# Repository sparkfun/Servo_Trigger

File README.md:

SparkFun Servo Trigger
========================================

[*SparkFun Servo Trigger (WIG-13118)*](https://www.sparkfun.com/products/13118)

The SparkFun Servo Trigger is a small robotics board that simplifies the control of hobby RC servo motors. 
When an external switch or logic signal changes state, the Servo Trigger is able to tell an attached servo motor to move from position A to position B. 
To use the Servo Trigger, you simply connect a hobby servo and a switch, then use the on-board potentiometers to adjust the start/stop positions and the transition time. 

Repository Contents
-------------------
* **/Docs** -  Programming notes
* **/Firmware** - Example firmware for running the Servo Trigger
* **/Hardware** - All Eagle design files (.brd, .sch)
* **/Production** - Test bed files and production panel files

License Information
-------------------
The hardware is released under [Creative Commons ShareAlike 4.0 International](https://creativecommons.org/licenses/by-sa/4.0/).
The code is beerware; if you see me (or any other SparkFun employee) at the local, and you've found our code helpful, please buy us a round!

Distributed as-is; no warranty is given.

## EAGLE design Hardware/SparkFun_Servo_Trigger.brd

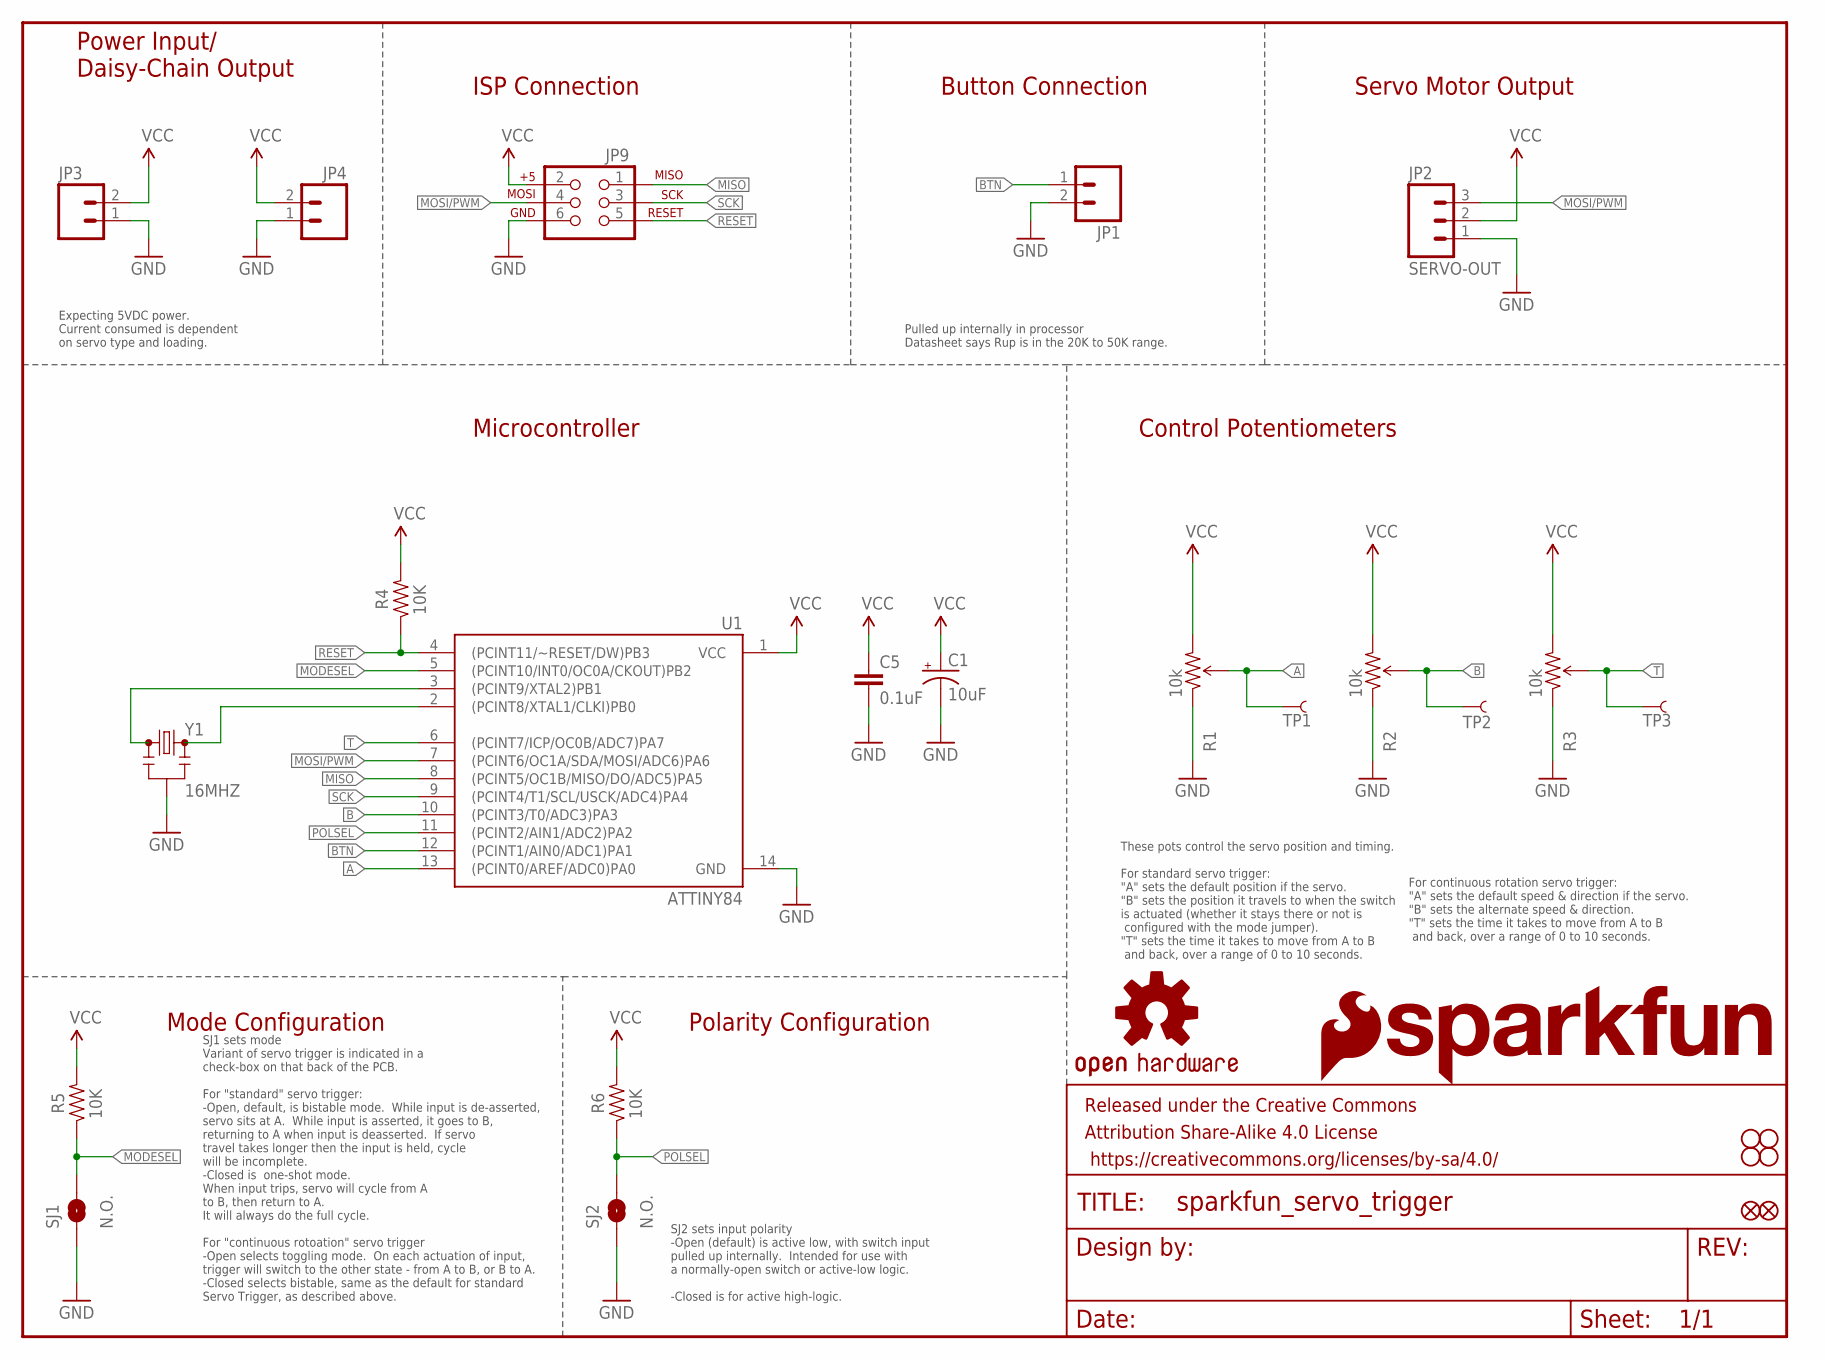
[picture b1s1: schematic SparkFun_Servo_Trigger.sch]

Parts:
C1: 10uF; EIA3216
C5: 0.1uF; 0603-CAP
FID1, FID2: FIDUCIAL1X2; FIDUCIAL-1X2
FRAME1: frame; CREATIVE_COMMONS
JP1, JP3, JP4: M021X02_NO_SILK; 1X02_NO_SILK
JP2: SERVO-OUT; 1X03_NO_SILK
JP9: AVR_SPI_PRG_6PTH; 2X3
LOGO1: OSHW-LOGOM; OSHW-LOGO-M
LOGO2: SFE_LOGO_NAME.2_INCH; SFE_LOGO_NAME_.2
LOGO3: SFE_LOGO_FLAME.2_INCH; SFE_LOGO_FLAME_.2
R1, R2, R3: 10k; TRIMPOT_5MM
R4, R5, R6: 10K; 0603-RES
SJ1, SJ2: N.O.; PAD-JUMPER-2-NO_YES_SILK
STANDOFF1, STANDOFF2, STANDOFF3, STANDOFF4: STAND-OFF
TP1, TP2, TP3: TEST-POINT3X4; PAD.03X.04
U1: ATTINY84; SO14
Y1: 16MHZ; RESONATOR-SMD

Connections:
A: R1.B (WIPER), TP1.P$1, U1.13 ((PCINT0/AREF/ADC0)PA0)
B: R2.B (WIPER), TP2.P$1, U1.10 ((PCINT3/T0/ADC3)PA3)
BTN: JP1.1, U1.12 ((PCINT1/AIN0/ADC1)PA1)
GND: C1.C (-), C5.2, JP1.2, JP2.1, JP3.1, JP4.1, JP9.6, R1.A (CCW), R2.A (CCW), R3.A (CCW), SJ1.1, SJ2.1, U1.14 (GND), Y1.2
MISO: JP9.1, U1.8 ((PCINT5/OC1B/MISO/DO/ADC5)PA5)
MODESEL: R5.1, SJ1.2, U1.5 ((PCINT10/INT0/OC0A/CKOUT)PB2)
MOSI/PWM: JP2.3, JP9.4, U1.7 ((PCINT6/OC1A/SDA/MOSI/ADC6)PA6)
unnamed: U1.3 ((PCINT9/XTAL2)PB1), Y1.1
unnamed: U1.2 ((PCINT8/XTAL1/CLKI)PB0), Y1.3
POLSEL: R6.1, SJ2.2, U1.11 ((PCINT2/AIN1/ADC2)PA2)
RESET: JP9.5, R4.1, U1.4 ((PCINT11/~RESET/DW)PB3)
SCK: JP9.3, U1.9 ((PCINT4/T1/SCL/USCK/ADC4)PA4)
T: R3.B (WIPER), TP3.P$1, U1.6 ((PCINT7/ICP/OC0B/ADC7)PA7)
VCC: C1.A (+), C5.1, JP2.2, JP3.2, JP4.2, JP9.2, R1.C (CW), R2.C (CW), R3.C (CW), R4.2, R5.2, R6.2, U1.1 (VCC)

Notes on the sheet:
Power Input/ Daisy-Chain Output
ISP Connection
Control Potentiometers
Microcontroller
Button Connection
Servo Motor Output
Mode Configuration
Polarity Configuration
SJ1 sets mode Variant of servo trigger is indicated in a check-box on that back of the PCB. For "standard" servo trigger: -Open, default, is bistable mode. While input is de-asserted, servo sits at A. While input is asserted, it goes to B, returning to A when input is deasserted. If servo travel ta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
SJ2 sets input polarity -Open (default) is active low, with switch input pulled up internally. Intended for use with a normally-open switch or active-low logic. -Closed is for active high-logic.
Pulled up internally in processor Datasheet says Rup is in the 20K to 50K range.
Expecting 5VDC power. Current consumed is dependent on servo type and loading.
These pots control the servo position and timing. For standard servo trigger: "A" sets the default position if the servo. "B" sets the position it travels to when the switch is actuated (whether it stays there or not is configured with the mode jumper). "T" sets the time it takes to move from A to 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
For continuous rotation servo trigger: "A" sets the default speed & direction if the servo. "B" sets the alternate speed & direction. "T" sets the time it takes to move from A to B and back, over a range of 0 to 10 seconds.

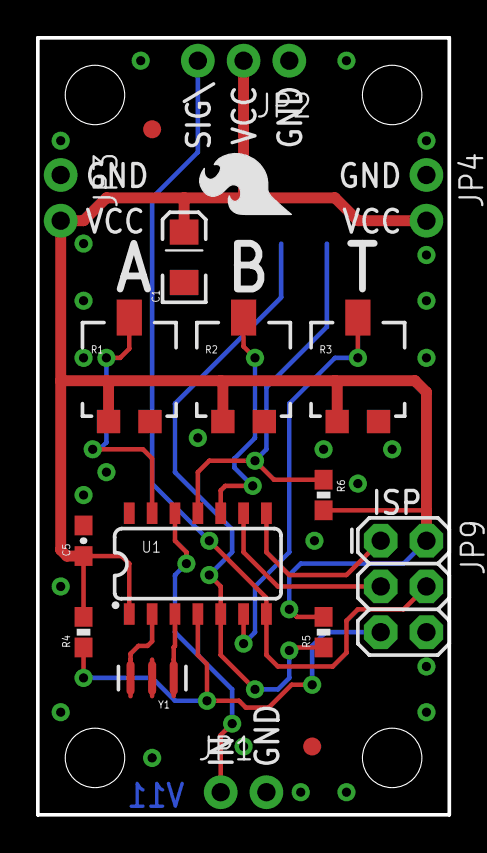
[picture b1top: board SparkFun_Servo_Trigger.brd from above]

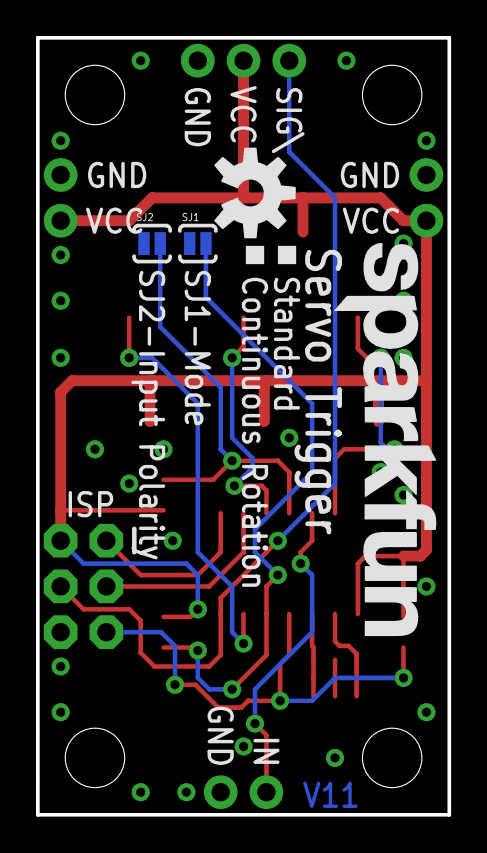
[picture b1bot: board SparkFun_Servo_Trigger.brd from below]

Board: 2 copper layers, 22.9 x 43.2 mm, 30 parts (7 on the bottom side), 14 nets.

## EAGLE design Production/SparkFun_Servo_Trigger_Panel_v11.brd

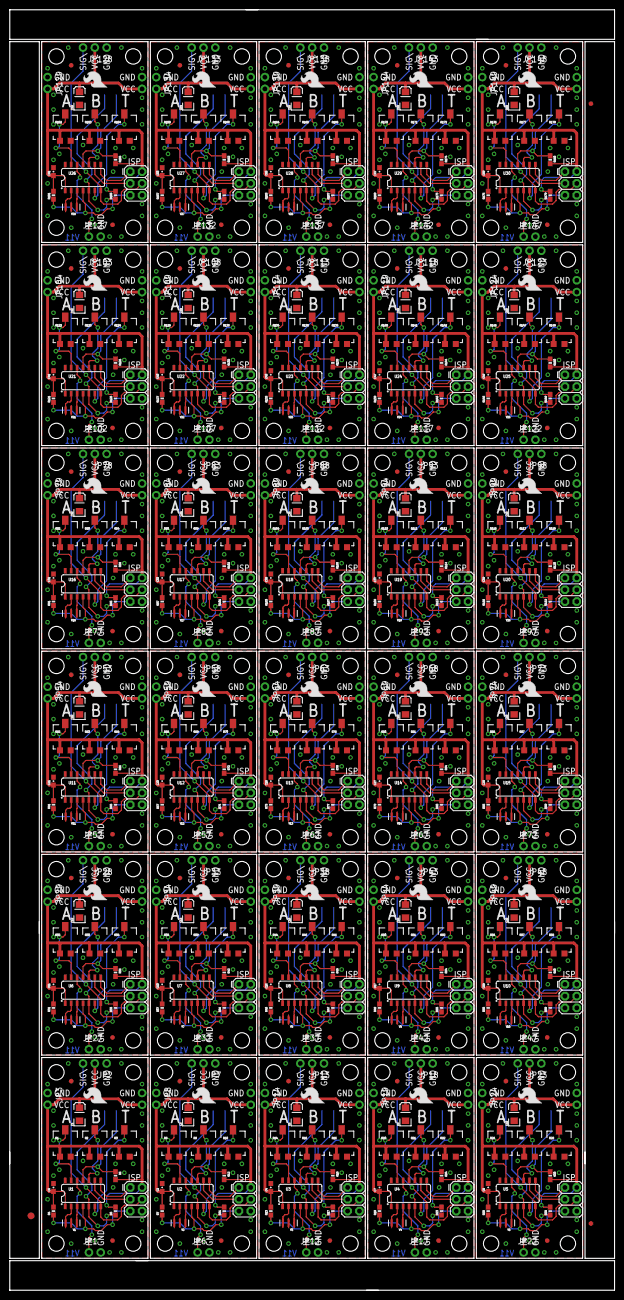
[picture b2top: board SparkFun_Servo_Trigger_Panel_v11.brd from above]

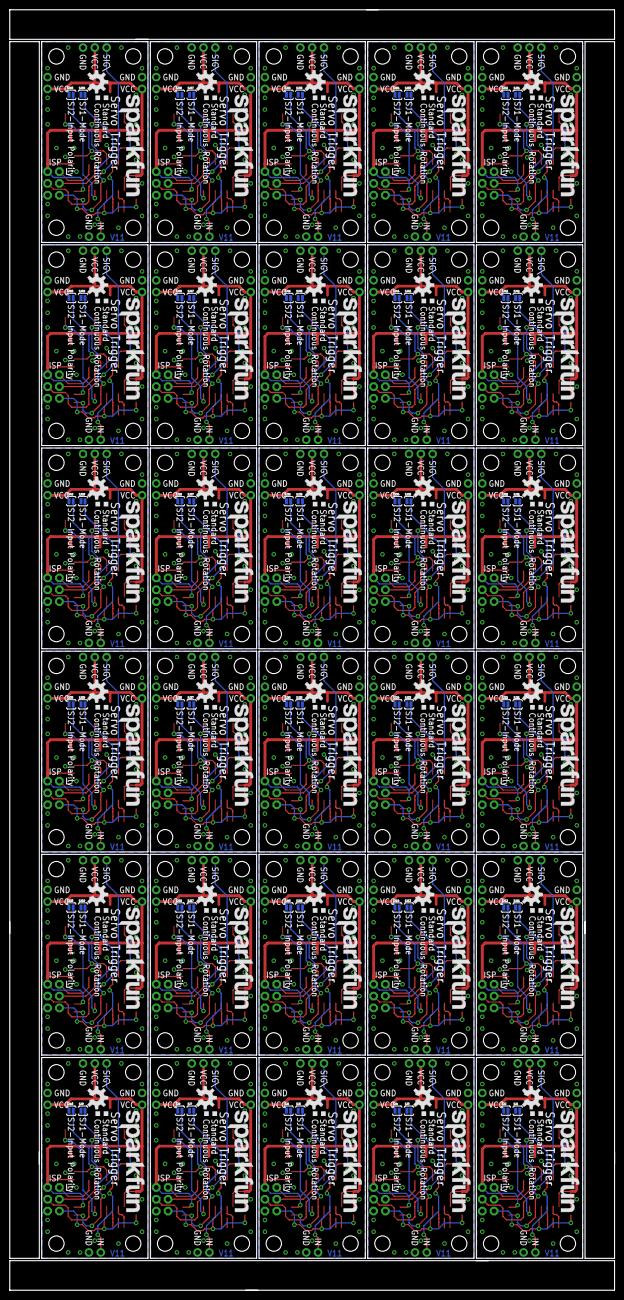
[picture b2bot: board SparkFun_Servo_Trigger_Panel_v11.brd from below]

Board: 2 copper layers, 130.0 x 275.3 mm, 873 parts (210 on the bottom side), 420 nets.

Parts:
C1, C3, C6, C8, C10, C12, C14, C16, C18, C20, C22, C24, C26, C28, C30, C32, C34, C36, C38, C40, C42, C44, C46, C48, C50, C52, C54, C56, C58, C60: 10uF; EIA3216
C2, C4, C5, C7, C9, C11, C13, C15, C17, C19, C21, C23, C25, C27, C29, C31, C33, C35, C37, C39, C41, C43, C45, C47, C49, C51, C53, C55, C57, C59: 0.1uF; 0603-CAP
E$1: FIDUCIAL-1.5X3
E$7, E$8: FIDUCIAL-1X2
FID1, FID2, FID3, FID4, FID5, FID6, FID7, FID8, FID9, FID10, FID11, FID12, FID13, FID14, FID15, FID16, FID17, FID18, FID19, FID20, FID21, FID22, FID23, FID24, FID25, FID26, FID27, FID28, FID29, FID30, FID31, FID32, FID33, FID34, FID35, FID36, FID37, FID38, FID39, FID40, FID41, FID42, FID43, FID44, FID45, FID46, FID47, FID48, FID49, FID50, FID51, FID52, FID53, FID54, FID55, FID56, FID57, FID58, FID59, FID60: FIDUCIAL1X2; FIDUCIAL-1X2
JP1, JP3, JP4, JP6, JP8, JP10, JP12, JP14, JP15, JP17, JP19, JP20, JP22, JP24, JP25, JP27, JP29, JP30, JP32, JP34, JP35, JP37, JP39, JP40, JP42, JP44, JP45, JP47, JP49, JP50, JP52, JP54, JP55, JP57, JP59, JP60, JP62, JP64, JP65, JP67, JP69, JP70, JP72, JP74, JP75, JP77, JP79, JP80, JP82, JP84, JP85, JP87, JP89, JP90, JP92, JP94, JP95, JP97, JP99, JP100, JP102, JP104, JP105, JP107, JP109, JP110, JP112, JP114, JP115, JP117, JP119, JP120, JP122, JP124, JP125, JP127, JP129, JP130, JP132, JP134, JP135, JP137, JP139, JP140, JP142, JP144, JP145, JP147, JP149, JP150: M021X02_NO_SILK; 1X02_NO_SILK
JP2, JP7, JP13, JP18, JP23, JP28, JP33, JP38, JP43, JP48, JP53, JP58, JP63, JP68, JP73, JP78, JP83, JP88, JP93, JP98, JP103, JP108, JP113, JP118, JP123, JP128, JP133, JP138, JP143, JP148: SERVO-OUT; 1X03_NO_SILK
JP5, JP9, JP11, JP16, JP21, JP26, JP31, JP36, JP41, JP46, JP51, JP56, JP61, JP66, JP71, JP76, JP81, JP86, JP91, JP96, JP101, JP106, JP111, JP116, JP121, JP126, JP131, JP136, JP141, JP146: 2X3
LOGO1, LOGO4, LOGO7, LOGO10, LOGO13, LOGO16, LOGO19, LOGO22, LOGO25, LOGO28, LOGO31, LOGO34, LOGO37, LOGO40, LOGO43, LOGO46, LOGO49, LOGO52, LOGO55, LOGO58, LOGO61, LOGO64, LOGO67, LOGO70, LOGO73, LOGO76, LOGO79, LOGO82, LOGO85, LOGO88: OSHW-LOGOM; OSHW-LOGO-M
LOGO2, LOGO5, LOGO8, LOGO11, LOGO14, LOGO17, LOGO20, LOGO23, LOGO26, LOGO29, LOGO32, LOGO35, LOGO38, LOGO41, LOGO44, LOGO47, LOGO50, LOGO53, LOGO56, LOGO59, LOGO62, LOGO65, LOGO68, LOGO71, LOGO74, LOGO77, LOGO80, LOGO83, LOGO86, LOGO89: SFE_LOGO_NAME.2_INCH; SFE_LOGO_NAME_.2
LOGO3, LOGO6, LOGO9, LOGO12, LOGO15, LOGO18, LOGO21, LOGO24, LOGO27, LOGO30, LOGO33, LOGO36, LOGO39, LOGO42, LOGO45, LOGO48, LOGO51, LOGO54, LOGO57, LOGO60, LOGO63, LOGO66, LOGO69, LOGO72, LOGO75, LOGO78, LOGO81, LOGO84, LOGO87, LOGO90: SFE_LOGO_FLAME.2_INCH; SFE_LOGO_FLAME_.2
R1, R2, R3, R8, R9, R10, R14, R15, R16, R20, R21, R22, R26, R27, R28, R32, R33, R34, R38, R39, R40, R44, R45, R46, R50, R51, R52, R56, R57, R58, R62, R63, R64, R68, R69, R70, R74, R75, R76, R80, R81, R82, R86, R87, R88, R92, R93, R94, R98, R99, R100, R104, R105, R106, R110, R111, R112, R116, R117, R118, R122, R123, R124, R128, R129, R130, R134, R135, R136, R140, R141, R142, R146, R147, R148, R152, R153, R154, R158, R159, R160, R164, R165, R166, R170, R171, R172, R176, R177, R178: 10k; TRIMPOT_5MM
R4, R5, R6, R7, R11, R12, R13, R17, R18, R19, R23, R24, R25, R29, R30, R31, R35, R36, R37, R41, R42, R43, R47, R48, R49, R53, R54, R55, R59, R60, R61, R65, R66, R67, R71, R72, R73, R77, R78, R79, R83, R84, R85, R89, R90, R91, R95, R96, R97, R101, R102, R103, R107, R108, R109, R113, R114, R115, R119, R120, R121, R125, R126, R127, R131, R132, R133, R137, R138, R139, R143, R144, R145, R149, R150, R151, R155, R156, R157, R161, R162, R163, R167, R168, R169, R173, R174, R175, R179, R180: 10K; 0603-RES
SJ1, SJ2, SJ3, SJ4, SJ5, SJ6, SJ7, SJ8, SJ9, SJ10, SJ11, SJ12, SJ13, SJ14, SJ15, SJ16, SJ17, SJ18, SJ19, SJ20, SJ21, SJ22, SJ23, SJ24, SJ25, SJ26, SJ27, SJ28, SJ29, SJ30, SJ31, SJ32, SJ33, SJ34, SJ35, SJ36, SJ37, SJ38, SJ39, SJ40, SJ41, SJ42, SJ43, SJ44, SJ45, SJ46, SJ47, SJ48, SJ49, SJ50, SJ51, SJ52, SJ53, SJ54, SJ55, SJ56, SJ57, SJ58, SJ59, SJ60: N.O.; PAD-JUMPER-2-NO_YES_SILK
STANDOFF1, STANDOFF2, STANDOFF3, STANDOFF4, STANDOFF5, STANDOFF6, STANDOFF7, STANDOFF8, STANDOFF9, STANDOFF10, STANDOFF11, STANDOFF12, STANDOFF13, STANDOFF14, STANDOFF15, STANDOFF16, STANDOFF17, STANDOFF18, STANDOFF19, STANDOFF20, STANDOFF21, STANDOFF22, STANDOFF23, STANDOFF24, STANDOFF25, STANDOFF26, STANDOFF27, STANDOFF28, STANDOFF29, STANDOFF30, STANDOFF31, STANDOFF32, STANDOFF33, STANDOFF34, STANDOFF35, STANDOFF36, STANDOFF37, STANDOFF38, STANDOFF39, STANDOFF40, STANDOFF41, STANDOFF42, STANDOFF43, STANDOFF44, STANDOFF45, STANDOFF46, STANDOFF47, STANDOFF48, STANDOFF49, STANDOFF50, STANDOFF51, STANDOFF52, STANDOFF53, STANDOFF54, STANDOFF55, STANDOFF56, STANDOFF57, STANDOFF58, STANDOFF59, STANDOFF60, STANDOFF61, STANDOFF62, STANDOFF63, STANDOFF64, STANDOFF65, STANDOFF66, STANDOFF67, STANDOFF68, STANDOFF69, STANDOFF70, STANDOFF71, STANDOFF72, STANDOFF73, STANDOFF74, STANDOFF75, STANDOFF76, STANDOFF77, STANDOFF78, STANDOFF79, STANDOFF80, STANDOFF81, STANDOFF82, STANDOFF83, STANDOFF84, STANDOFF85, STANDOFF86, STANDOFF87, STANDOFF88, STANDOFF89, STANDOFF90, STANDOFF91, STANDOFF92, STANDOFF93, STANDOFF94, STANDOFF95, STANDOFF96, STANDOFF97, STANDOFF98, STANDOFF99, STANDOFF100, STANDOFF101, STANDOFF102, STANDOFF103, STANDOFF104, STANDOFF105, STANDOFF106, STANDOFF107, STANDOFF108, STANDOFF109, STANDOFF110, STANDOFF111, STANDOFF112, STANDOFF113, STANDOFF114, STANDOFF115, STANDOFF116, STANDOFF117, STANDOFF118, STANDOFF119, STANDOFF120: STAND-OFF
TP1, TP2, TP3, TP4, TP5, TP6, TP7, TP8, TP9, TP10, TP11, TP12, TP13, TP14, TP15, TP16, TP17, TP18, TP19, TP20, TP21, TP22, TP23, TP24, TP25, TP26, TP27, TP28, TP29, TP30, TP31, TP32, TP33, TP34, TP35, TP36, TP37, TP38, TP39, TP40, TP41, TP42, TP43, TP44, TP45, TP46, TP47, TP48, TP49, TP50, TP51, TP52, TP53, TP54, TP55, TP56, TP57, TP58, TP59, TP60, TP61, TP62, TP63, TP64, TP65, TP66, TP67, TP68, TP69, TP70, TP71, TP72, TP73, TP74, TP75, TP76, TP77, TP78, TP79, TP80, TP81, TP82, TP83, TP84, TP85, TP86, TP87, TP88, TP89, TP90: TEST-POINT3X4; PAD.03X.04
U1, U2, U3, U4, U5, U6, U7, U8, U9, U10, U11, U12, U13, U14, U15, U16, U17, U18, U19, U20, U21, U22, U23, U24, U25, U26, U27, U28, U29, U30: ATTINY84; SO14
Y1, Y2, Y3, Y4, Y5, Y6, Y7, Y8, Y9, Y10, Y11, Y12, Y13, Y14, Y15, Y16, Y17, Y18, Y19, Y20, Y21, Y22, Y23, Y24, Y25, Y26, Y27, Y28, Y29, Y30: 16MHZ; RESONATOR-SMD

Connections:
A: R1.B, TP1.P$1, U1.13
A1: R8.B, TP4.P$1, U2.13
A2: R14.B, TP7.P$1, U3.13
A3: R20.B, TP10.P$1, U4.13
A4: R26.B, TP13.P$1, U5.13
A5: R32.B, TP16.P$1, U6.13
A6: R38.B, TP19.P$1, U7.13
A7: R44.B, TP22.P$1, U8.13
A8: R50.B, TP25.P$1, U9.13
A9: R56.B, TP28.P$1, U10.13
A10: R62.B, TP31.P$1, U11.13
A11: R68.B, TP34.P$1, U12.13
A12: R74.B, TP37.P$1, U13.13
A13: R80.B, TP40.P$1, U14.13
A14: R86.B, TP43.P$1, U15.13
A15: R92.B, TP46.P$1, U16.13
A16: R98.B, TP49.P$1, U17.13
A17: R104.B, TP52.P$1, U18.13
A18: R110.B, TP55.P$1, U19.13
A19: R116.B, TP58.P$1, U20.13
A20: R122.B, TP61.P$1, U21.13
A21: R128.B, TP64.P$1, U22.13
A22: R134.B, TP67.P$1, U23.13
A23: R140.B, TP70.P$1, U24.13
A24: R146.B, TP73.P$1, U25.13
A25: R152.B, TP76.P$1, U26.13
A26: R158.B, TP79.P$1, U27.13
A27: R164.B, TP82.P$1, U28.13
A28: R170.B, TP85.P$1, U29.13
A29: R176.B, TP88.P$1, U30.13
B: R2.B, TP2.P$1, U1.10
B1: R9.B, TP5.P$1, U2.10
B2: R15.B, TP8.P$1, U3.10
B3: R21.B, TP11.P$1, U4.10
B4: R27.B, TP14.P$1, U5.10
B5: R33.B, TP17.P$1, U6.10
B6: R39.B, TP20.P$1, U7.10
B7: R45.B, TP23.P$1, U8.10
B8: R51.B, TP26.P$1, U9.10
B9: R57.B, TP29.P$1, U10.10
B10: R63.B, TP32.P$1, U11.10
B11: R69.B, TP35.P$1, U12.10
B12: R75.B, TP38.P$1, U13.10
B13: R81.B, TP41.P$1, U14.10
B14: R87.B, TP44.P$1, U15.10
B15: R93.B, TP47.P$1, U16.10
B16: R99.B, TP50.P$1, U17.10
B17: R105.B, TP53.P$1, U18.10
B18: R111.B, TP56.P$1, U19.10
B19: R117.B, TP59.P$1, U20.10
B20: R123.B, TP62.P$1, U21.10
B21: R129.B, TP65.P$1, U22.10
B22: R135.B, TP68.P$1, U23.10
B23: R141.B, TP71.P$1, U24.10
B24: R147.B, TP74.P$1, U25.10
B25: R153.B, TP77.P$1, U26.10
B26: R159.B, TP80.P$1, U27.10
B27: R165.B, TP83.P$1, U28.10
B28: R171.B, TP86.P$1, U29.10
B29: R177.B, TP89.P$1, U30.10
BTN: JP1.1, U1.12
BTN1: JP6.1, U2.12
BTN2: JP12.1, U3.12
BTN3: JP17.1, U4.12
BTN4: JP22.1, U5.12
BTN5: JP27.1, U6.12
BTN6: JP32.1, U7.12
BTN7: JP37.1, U8.12
BTN8: JP42.1, U9.12
BTN9: JP47.1, U10.12
BTN10: JP52.1, U11.12
BTN11: JP57.1, U12.12
BTN12: JP62.1, U13.12
BTN13: JP67.1, U14.12
BTN14: JP72.1, U15.12
BTN15: JP77.1, U16.12
BTN16: JP82.1, U17.12
BTN17: JP87.1, U18.12
BTN18: JP92.1, U19.12
BTN19: JP97.1, U20.12
BTN20: JP102.1, U21.12
BTN21: JP107.1, U22.12
BTN22: JP112.1, U23.12
BTN23: JP117.1, U24.12
BTN24: JP122.1, U25.12
BTN25: JP127.1, U26.12
BTN26: JP132.1, U27.12
BTN27: JP137.1, U28.12
BTN28: JP142.1, U29.12
BTN29: JP147.1, U30.12
GND: C1.C, C5.2, JP1.2, JP2.1, JP3.1, JP4.1, JP9.6, R1.A, R2.A, R3.A, SJ1.1, SJ2.1, U1.14, Y1.2
GND1: C2.2, C3.C, JP5.6, JP6.2, JP7.1, JP8.1, JP10.1, R8.A, R9.A, R10.A, SJ3.1, SJ4.1, U2.14, Y2.2
GND2: C4.2, C6.C, JP11.6, JP12.2, JP13.1, JP14.1, JP15.1, R14.A, R15.A, R16.A, SJ5.1, SJ6.1, U3.14, Y3.2
GND3: C7.2, C8.C, JP16.6, JP17.2, JP18.1, JP19.1, JP20.1, R20.A, R21.A, R22.A, SJ7.1, SJ8.1, U4.14, Y4.2
GND4: C9.2, C10.C, JP21.6, JP22.2, JP23.1, JP24.1, JP25.1, R26.A, R27.A, R28.A, SJ9.1, SJ10.1, U5.14, Y5.2
GND5: C11.2, C12.C, JP26.6, JP27.2, JP28.1, JP29.1, JP30.1, R32.A, R33.A, R34.A, SJ11.1, SJ12.1, U6.14, Y6.2
GND6: C13.2, C14.C, JP31.6, JP32.2, JP33.1, JP34.1, JP35.1, R38.A, R39.A, R40.A, SJ13.1, SJ14.1, U7.14, Y7.2
GND7: C15.2, C16.C, JP36.6, JP37.2, JP38.1, JP39.1, JP40.1, R44.A, R45.A, R46.A, SJ15.1, SJ16.1, U8.14, Y8.2
GND8: C17.2, C18.C, JP41.6, JP42.2, JP43.1, JP44.1, JP45.1, R50.A, R51.A, R52.A, SJ17.1, SJ18.1, U9.14, Y9.2
GND9: C19.2, C20.C, JP46.6, JP47.2, JP48.1, JP49.1, JP50.1, R56.A, R57.A, R58.A, SJ19.1, SJ20.1, U10.14, Y10.2
GND10: C21.2, C22.C, JP51.6, JP52.2, JP53.1, JP54.1, JP55.1, R62.A, R63.A, R64.A, SJ21.1, SJ22.1, U11.14, Y11.2
GND11: C23.2, C24.C, JP56.6, JP57.2, JP58.1, JP59.1, JP60.1, R68.A, R69.A, R70.A, SJ23.1, SJ24.1, U12.14, Y12.2
GND12: C25.2, C26.C, JP61.6, JP62.2, JP63.1, JP64.1, JP65.1, R74.A, R75.A, R76.A, SJ25.1, SJ26.1, U13.14, Y13.2
GND13: C27.2, C28.C, JP66.6, JP67.2, JP68.1, JP69.1, JP70.1, R80.A, R81.A, R82.A, SJ27.1, SJ28.1, U14.14, Y14.2
GND14: C29.2, C30.C, JP71.6, JP72.2, JP73.1, JP74.1, JP75.1, R86.A, R87.A, R88.A, SJ29.1, SJ30.1, U15.14, Y15.2
GND15: C31.2, C32.C, JP76.6, JP77.2, JP78.1, JP79.1, JP80.1, R92.A, R93.A, R94.A, SJ31.1, SJ32.1, U16.14, Y16.2
GND16: C33.2, C34.C, JP81.6, JP82.2, JP83.1, JP84.1, JP85.1, R98.A, R99.A, R100.A, SJ33.1, SJ34.1, U17.14, Y17.2
GND17: C35.2, C36.C, JP86.6, JP87.2, JP88.1, JP89.1, JP90.1, R104.A, R105.A, R106.A, SJ35.1, SJ36.1, U18.14, Y18.2
GND18: C37.2, C38.C, JP91.6, JP92.2, JP93.1, JP94.1, JP95.1, R110.A, R111.A, R112.A, SJ37.1, SJ38.1, U19.14, Y19.2
GND19: C39.2, C40.C, JP96.6, JP97.2, JP98.1, JP99.1, JP100.1, R116.A, R117.A, R118.A, SJ39.1, SJ40.1, U20.14, Y20.2
GND20: C41.2, C42.C, JP101.6, JP102.2, JP103.1, JP104.1, JP105.1, R122.A, R123.A, R124.A, SJ41.1, SJ42.1, U21.14, Y21.2
GND21: C43.2, C44.C, JP106.6, JP107.2, JP108.1, JP109.1, JP110.1, R128.A, R129.A, R130.A, SJ43.1, SJ44.1, U22.14, Y22.2
GND22: C45.2, C46.C, JP111.6, JP112.2, JP113.1, JP114.1, JP115.1, R134.A, R135.A, R136.A, SJ45.1, SJ46.1, U23.14, Y23.2
GND23: C47.2, C48.C, JP116.6, JP117.2, JP118.1, JP119.1, JP120.1, R140.A, R141.A, R142.A, SJ47.1, SJ48.1, U24.14, Y24.2
GND24: C49.2, C50.C, JP121.6, JP122.2, JP123.1, JP124.1, JP125.1, R146.A, R147.A, R148.A, SJ49.1, SJ50.1, U25.14, Y25.2
GND25: C51.2, C52.C, JP126.6, JP127.2, JP128.1, JP129.1, JP130.1, R152.A, R153.A, R154.A, SJ51.1, SJ52.1, U26.14, Y26.2
GND26: C53.2, C54.C, JP131.6, JP132.2, JP133.1, JP134.1, JP135.1, R158.A, R159.A, R160.A, SJ53.1, SJ54.1, U27.14, Y27.2
GND27: C55.2, C56.C, JP136.6, JP137.2, JP138.1, JP139.1, JP140.1, R164.A, R165.A, R166.A, SJ55.1, SJ56.1, U28.14, Y28.2
GND28: C57.2, C58.C, JP141.6, JP142.2, JP143.1, JP144.1, JP145.1, R170.A, R171.A, R172.A, SJ57.1, SJ58.1, U29.14, Y29.2
GND29: C59.2, C60.C, JP146.6, JP147.2, JP148.1, JP149.1, JP150.1, R176.A, R177.A, R178.A, SJ59.1, SJ60.1, U30.14, Y30.2
MISO: JP9.1, U1.8
MISO1: JP5.1, U2.8
MISO2: JP11.1, U3.8
MISO3: JP16.1, U4.8
MISO4: JP21.1, U5.8
MISO5: JP26.1, U6.8
MISO6: JP31.1, U7.8
MISO7: JP36.1, U8.8
MISO8: JP41.1, U9.8
MISO9: JP46.1, U10.8
MISO10: JP51.1, U11.8
MISO11: JP56.1, U12.8
MISO12: JP61.1, U13.8
MISO13: JP66.1, U14.8
MISO14: JP71.1, U15.8
MISO15: JP76.1, U16.8
MISO16: JP81.1, U17.8
MISO17: JP86.1, U18.8
MISO18: JP91.1, U19.8
MISO19: JP96.1, U20.8
MISO20: JP101.1, U21.8
MISO21: JP106.1, U22.8
MISO22: JP111.1, U23.8
MISO23: JP116.1, U24.8
MISO24: JP121.1, U25.8
MISO25: JP126.1, U26.8
MISO26: JP131.1, U27.8
MISO27: JP136.1, U28.8
MISO28: JP141.1, U29.8
MISO29: JP146.1, U30.8
MODESEL: R5.1, SJ1.2, U1.5
MODESEL1: R11.1, SJ3.2, U2.5
MODESEL2: R17.1, SJ5.2, U3.5
MODESEL3: R23.1, SJ7.2, U4.5
MODESEL4: R29.1, SJ9.2, U5.5
MODESEL5: R35.1, SJ11.2, U6.5
MODESEL6: R41.1, SJ13.2, U7.5
MODESEL7: R47.1, SJ15.2, U8.5
MODESEL8: R53.1, SJ17.2, U9.5
MODESEL9: R59.1, SJ19.2, U10.5
MODESEL10: R65.1, SJ21.2, U11.5
MODESEL11: R71.1, SJ23.2, U12.5
MODESEL12: R77.1, SJ25.2, U13.5
MODESEL13: R83.1, SJ27.2, U14.5
MODESEL14: R89.1, SJ29.2, U15.5
MODESEL15: R95.1, SJ31.2, U16.5
MODESEL16: R101.1, SJ33.2, U17.5
MODESEL17: R107.1, SJ35.2, U18.5
MODESEL18: R113.1, SJ37.2, U19.5
MODESEL19: R119.1, SJ39.2, U20.5
MODESEL20: R125.1, SJ41.2, U21.5
MODESEL21: R131.1, SJ43.2, U22.5
MODESEL22: R137.1, SJ45.2, U23.5
MODESEL23: R143.1, SJ47.2, U24.5
MODESEL24: R149.1, SJ49.2, U25.5
MODESEL25: R155.1, SJ51.2, U26.5
MODESEL26: R161.1, SJ53.2, U27.5
MODESEL27: R167.1, SJ55.2, U28.5
MODESEL28: R173.1, SJ57.2, U29.5
MODESEL29: R179.1, SJ59.2, U30.5
MOSI/PWM: JP2.3, JP9.4, U1.7
MOSI/PWM1: JP5.4, JP7.3, U2.7
MOSI/PWM2: JP11.4, JP13.3, U3.7
MOSI/PWM3: JP16.4, JP18.3, U4.7
MOSI/PWM4: JP21.4, JP23.3, U5.7
MOSI/PWM5: JP26.4, JP28.3, U6.7
MOSI/PWM6: JP31.4, JP33.3, U7.7
MOSI/PWM7: JP36.4, JP38.3, U8.7
MOSI/PWM8: JP41.4, JP43.3, U9.7
MOSI/PWM9: JP46.4, JP48.3, U10.7
MOSI/PWM10: JP51.4, JP53.3, U11.7
MOSI/PWM11: JP56.4, JP58.3, U12.7
MOSI/PWM12: JP61.4, JP63.3, U13.7
MOSI/PWM13: JP66.4, JP68.3, U14.7
MOSI/PWM14: JP71.4, JP73.3, U15.7
MOSI/PWM15: JP76.4, JP78.3, U16.7
MOSI/PWM16: JP81.4, JP83.3, U17.7
MOSI/PWM17: JP86.4, JP88.3, U18.7
MOSI/PWM18: JP91.4, JP93.3, U19.7
MOSI/PWM19: JP96.4, JP98.3, U20.7
MOSI/PWM20: JP101.4, JP103.3, U21.7
MOSI/PWM21: JP106.4, JP108.3, U22.7
MOSI/PWM22: JP111.4, JP113.3, U23.7
MOSI/PWM23: JP116.4, JP118.3, U24.7
MOSI/PWM24: JP121.4, JP123.3, U25.7
MOSI/PWM25: JP126.4, JP128.3, U26.7
MOSI/PWM26: JP131.4, JP133.3, U27.7
MOSI/PWM27: JP136.4, JP138.3, U28.7
MOSI/PWM28: JP141.4, JP143.3, U29.7
MOSI/PWM29: JP146.4, JP148.3, U30.7
unnamed: U2.3, Y2.1
unnamed: U2.2, Y2.3
unnamed: U1.3, Y1.1
unnamed: U1.2, Y1.3
unnamed: U3.3, Y3.1
unnamed: U3.2, Y3.3
unnamed: U4.3, Y4.1
unnamed: U4.2, Y4.3
unnamed: U5.3, Y5.1
unnamed: U5.2, Y5.3
unnamed: U6.3, Y6.1
unnamed: U6.2, Y6.3
unnamed: U7.3, Y7.1
unnamed: U7.2, Y7.3
unnamed: U8.3, Y8.1
unnamed: U8.2, Y8.3
unnamed: U9.3, Y9.1
unnamed: U9.2, Y9.3
unnamed: U10.3, Y10.1
unnamed: U10.2, Y10.3
unnamed: U11.3, Y11.1
unnamed: U11.2, Y11.3
unnamed: U12.3, Y12.1
unnamed: U12.2, Y12.3
unnamed: U13.3, Y13.1
unnamed: U13.2, Y13.3
unnamed: U14.3, Y14.1
unnamed: U14.2, Y14.3
unnamed: U15.3, Y15.1
unnamed: U15.2, Y15.3
unnamed: U16.3, Y16.1
unnamed: U16.2, Y16.3
unnamed: U17.3, Y17.1
unnamed: U17.2, Y17.3
unnamed: U18.3, Y18.1
unnamed: U18.2, Y18.3
unnamed: U19.3, Y19.1
unnamed: U19.2, Y19.3
unnamed: U20.3, Y20.1
unnamed: U20.2, Y20.3
unnamed: U21.3, Y21.1
unnamed: U21.2, Y21.3
unnamed: U22.3, Y22.1
unnamed: U22.2, Y22.3
unnamed: U23.3, Y23.1
unnamed: U23.2, Y23.3
unnamed: U24.3, Y24.1
unnamed: U24.2, Y24.3
unnamed: U25.3, Y25.1
unnamed: U25.2, Y25.3
unnamed: U26.3, Y26.1
unnamed: U26.2, Y26.3
unnamed: U27.3, Y27.1
unnamed: U27.2, Y27.3
unnamed: U28.3, Y28.1
unnamed: U28.2, Y28.3
unnamed: U29.3, Y29.1
unnamed: U29.2, Y29.3
unnamed: U30.3, Y30.1
unnamed: U30.2, Y30.3
POLSEL: R6.1, SJ2.2, U1.11
POLSEL1: R12.1, SJ4.2, U2.11
POLSEL2: R18.1, SJ6.2, U3.11
POLSEL3: R24.1, SJ8.2, U4.11
POLSEL4: R30.1, SJ10.2, U5.11
POLSEL5: R36.1, SJ12.2, U6.11
POLSEL6: R42.1, SJ14.2, U7.11
POLSEL7: R48.1, SJ16.2, U8.11
POLSEL8: R54.1, SJ18.2, U9.11
POLSEL9: R60.1, SJ20.2, U10.11
POLSEL10: R66.1, SJ22.2, U11.11
POLSEL11: R72.1, SJ24.2, U12.11
POLSEL12: R78.1, SJ26.2, U13.11
POLSEL13: R84.1, SJ28.2, U14.11
POLSEL14: R90.1, SJ30.2, U15.11
POLSEL15: R96.1, SJ32.2, U16.11
POLSEL16: R102.1, SJ34.2, U17.11
POLSEL17: R108.1, SJ36.2, U18.11
POLSEL18: R114.1, SJ38.2, U19.11
POLSEL19: R120.1, SJ40.2, U20.11
POLSEL20: R126.1, SJ42.2, U21.11
POLSEL21: R132.1, SJ44.2, U22.11
POLSEL22: R138.1, SJ46.2, U23.11
POLSEL23: R144.1, SJ48.2, U24.11
POLSEL24: R150.1, SJ50.2, U25.11
POLSEL25: R156.1, SJ52.2, U26.11
POLSEL26: R162.1, SJ54.2, U27.11
POLSEL27: R168.1, SJ56.2, U28.11
POLSEL28: R174.1, SJ58.2, U29.11
POLSEL29: R180.1, SJ60.2, U30.11
RESET: JP9.5, R4.1, U1.4
RESET1: JP5.5, R7.1, U2.4
RESET2: JP11.5, R13.1, U3.4
RESET3: JP16.5, R19.1, U4.4
RESET4: JP21.5, R25.1, U5.4
RESET5: JP26.5, R31.1, U6.4
RESET6: JP31.5, R37.1, U7.4
RESET7: JP36.5, R43.1, U8.4
RESET8: JP41.5, R49.1, U9.4
RESET9: JP46.5, R55.1, U10.4
RESET10: JP51.5, R61.1, U11.4
RESET11: JP56.5, R67.1, U12.4
RESET12: JP61.5, R73.1, U13.4
RESET13: JP66.5, R79.1, U14.4
RESET14: JP71.5, R85.1, U15.4
RESET15: JP76.5, R91.1, U16.4
RESET16: JP81.5, R97.1, U17.4
RESET17: JP86.5, R103.1, U18.4
RESET18: JP91.5, R109.1, U19.4
RESET19: JP96.5, R115.1, U20.4
RESET20: JP101.5, R121.1, U21.4
RESET21: JP106.5, R127.1, U22.4
RESET22: JP111.5, R133.1, U23.4
RESET23: JP116.5, R139.1, U24.4
RESET24: JP121.5, R145.1, U25.4
RESET25: JP126.5, R151.1, U26.4
RESET26: JP131.5, R157.1, U27.4
RESET27: JP136.5, R163.1, U28.4
RESET28: JP141.5, R169.1, U29.4
RESET29: JP146.5, R175.1, U30.4
SCK: JP9.3, U1.9
SCK1: JP5.3, U2.9
SCK2: JP11.3, U3.9
SCK3: JP16.3, U4.9
SCK4: JP21.3, U5.9
SCK5: JP26.3, U6.9
SCK6: JP31.3, U7.9
SCK7: JP36.3, U8.9
SCK8: JP41.3, U9.9
SCK9: JP46.3, U10.9
SCK10: JP51.3, U11.9
SCK11: JP56.3, U12.9
SCK12: JP61.3, U13.9
SCK13: JP66.3, U14.9
SCK14: JP71.3, U15.9
SCK15: JP76.3, U16.9
SCK16: JP81.3, U17.9
SCK17: JP86.3, U18.9
SCK18: JP91.3, U19.9
SCK19: JP96.3, U20.9
SCK20: JP101.3, U21.9
SCK21: JP106.3, U22.9
SCK22: JP111.3, U23.9
SCK23: JP116.3, U24.9
SCK24: JP121.3, U25.9
SCK25: JP126.3, U26.9
SCK26: JP131.3, U27.9
SCK27: JP136.3, U28.9
SCK28: JP141.3, U29.9
SCK29: JP146.3, U30.9
T: R3.B, TP3.P$1, U1.6
T1: R10.B, TP6.P$1, U2.6
T2: R16.B, TP9.P$1, U3.6
T3: R22.B, TP12.P$1, U4.6
T4: R28.B, TP15.P$1, U5.6
T5: R34.B, TP18.P$1, U6.6
T6: R40.B, TP21.P$1, U7.6
T7: R46.B, TP24.P$1, U8.6
T8: R52.B, TP27.P$1, U9.6
T9: R58.B, TP30.P$1, U10.6
T10: R64.B, TP33.P$1, U11.6
T11: R70.B, TP36.P$1, U12.6
T12: R76.B, TP39.P$1, U13.6
T13: R82.B, TP42.P$1, U14.6
T14: R88.B, TP45.P$1, U15.6
T15: R94.B, TP48.P$1, U16.6
T16: R100.B, TP51.P$1, U17.6
T17: R106.B, TP54.P$1, U18.6
T18: R112.B, TP57.P$1, U19.6
T19: R118.B, TP60.P$1, U20.6
T20: R124.B, TP63.P$1, U21.6
T21: R130.B, TP66.P$1, U22.6
T22: R136.B, TP69.P$1, U23.6
T23: R142.B, TP72.P$1, U24.6
T24: R148.B, TP75.P$1, U25.6
T25: R154.B, TP78.P$1, U26.6
T26: R160.B, TP81.P$1, U27.6
T27: R166.B, TP84.P$1, U28.6
T28: R172.B, TP87.P$1, U29.6
T29: R178.B, TP90.P$1, U30.6
VCC: C1.A, C5.1, JP2.2, JP3.2, JP4.2, JP9.2, R1.C, R2.C, R3.C, R4.2, R5.2, R6.2, U1.1
VCC1: C2.1, C3.A, JP5.2, JP7.2, JP8.2, JP10.2, R7.2, R8.C, R9.C, R10.C, R11.2, R12.2, U2.1
VCC2: C4.1, C6.A, JP11.2, JP13.2, JP14.2, JP15.2, R13.2, R14.C, R15.C, R16.C, R17.2, R18.2, U3.1
VCC3: C7.1, C8.A, JP16.2, JP18.2, JP19.2, JP20.2, R19.2, R20.C, R21.C, R22.C, R23.2, R24.2, U4.1
VCC4: C9.1, C10.A, JP21.2, JP23.2, JP24.2, JP25.2, R25.2, R26.C, R27.C, R28.C, R29.2, R30.2, U5.1
VCC5: C11.1, C12.A, JP26.2, JP28.2, JP29.2, JP30.2, R31.2, R32.C, R33.C, R34.C, R35.2, R36.2, U6.1
VCC6: C13.1, C14.A, JP31.2, JP33.2, JP34.2, JP35.2, R37.2, R38.C, R39.C, R40.C, R41.2, R42.2, U7.1
VCC7: C15.1, C16.A, JP36.2, JP38.2, JP39.2, JP40.2, R43.2, R44.C, R45.C, R46.C, R47.2, R48.2, U8.1
VCC8: C17.1, C18.A, JP41.2, JP43.2, JP44.2, JP45.2, R49.2, R50.C, R51.C, R52.C, R53.2, R54.2, U9.1
VCC9: C19.1, C20.A, JP46.2, JP48.2, JP49.2, JP50.2, R55.2, R56.C, R57.C, R58.C, R59.2, R60.2, U10.1
VCC10: C21.1, C22.A, JP51.2, JP53.2, JP54.2, JP55.2, R61.2, R62.C, R63.C, R64.C, R65.2, R66.2, U11.1
VCC11: C23.1, C24.A, JP56.2, JP58.2, JP59.2, JP60.2, R67.2, R68.C, R69.C, R70.C, R71.2, R72.2, U12.1
VCC12: C25.1, C26.A, JP61.2, JP63.2, JP64.2, JP65.2, R73.2, R74.C, R75.C, R76.C, R77.2, R78.2, U13.1
VCC13: C27.1, C28.A, JP66.2, JP68.2, JP69.2, JP70.2, R79.2, R80.C, R81.C, R82.C, R83.2, R84.2, U14.1
VCC14: C29.1, C30.A, JP71.2, JP73.2, JP74.2, JP75.2, R85.2, R86.C, R87.C, R88.C, R89.2, R90.2, U15.1
VCC15: C31.1, C32.A, JP76.2, JP78.2, JP79.2, JP80.2, R91.2, R92.C, R93.C, R94.C, R95.2, R96.2, U16.1
VCC16: C33.1, C34.A, JP81.2, JP83.2, JP84.2, JP85.2, R97.2, R98.C, R99.C, R100.C, R101.2, R102.2, U17.1
VCC17: C35.1, C36.A, JP86.2, JP88.2, JP89.2, JP90.2, R103.2, R104.C, R105.C, R106.C, R107.2, R108.2, U18.1
VCC18: C37.1, C38.A, JP91.2, JP93.2, JP94.2, JP95.2, R109.2, R110.C, R111.C, R112.C, R113.2, R114.2, U19.1
VCC19: C39.1, C40.A, JP96.2, JP98.2, JP99.2, JP100.2, R115.2, R116.C, R117.C, R118.C, R119.2, R120.2, U20.1
VCC20: C41.1, C42.A, JP101.2, JP103.2, JP104.2, JP105.2, R121.2, R122.C, R123.C, R124.C, R125.2, R126.2, U21.1
VCC21: C43.1, C44.A, JP106.2, JP108.2, JP109.2, JP110.2, R127.2, R128.C, R129.C, R130.C, R131.2, R132.2, U22.1
VCC22: C45.1, C46.A, JP111.2, JP113.2, JP114.2, JP115.2, R133.2, R134.C, R135.C, R136.C, R137.2, R138.2, U23.1
VCC23: C47.1, C48.A, JP116.2, JP118.2, JP119.2, JP120.2, R139.2, R140.C, R141.C, R142.C, R143.2, R144.2, U24.1
VCC24: C49.1, C50.A, JP121.2, JP123.2, JP124.2, JP125.2, R145.2, R146.C, R147.C, R148.C, R149.2, R150.2, U25.1
VCC25: C51.1, C52.A, JP126.2, JP128.2, JP129.2, JP130.2, R151.2, R152.C, R153.C, R154.C, R155.2, R156.2, U26.1
VCC26: C53.1, C54.A, JP131.2, JP133.2, JP134.2, JP135.2, R157.2, R158.C, R159.C, R160.C, R161.2, R162.2, U27.1
VCC27: C55.1, C56.A, JP136.2, JP138.2, JP139.2, JP140.2, R163.2, R164.C, R165.C, R166.C, R167.2, R168.2, U28.1
VCC28: C57.1, C58.A, JP141.2, JP143.2, JP144.2, JP145.2, R169.2, R170.C, R171.C, R172.C, R173.2, R174.2, U29.1
VCC29: C59.1, C60.A, JP146.2, JP148.2, JP149.2, JP150.2, R175.2, R176.C, R177.C, R178.C, R179.2, R180.2, U30.1

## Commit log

2014-07-18 Initial Commit
    Boilerplate files and placeholders
2014-07-18 Adding draft of board files
2014-07-18 Adding draft of firmware.
    Working but very limited in features.
2014-07-23 Redid ramp generation.
    Using constant traversal time rather than constant rate. Moved to
    higher-precision math, too.
2014-09-11 PCB Work in progress
    Routed board, set up basic jumpers.
2014-09-12 PCB updates
2014-09-15 Updating parts
    I'd cut & pasted the tiny programmer, which used outdated parts.
    Updated to 0603 resistors & caps, using resonator instead of crystal,
    etc.
2014-10-16 Minor updates.
    Evaluating prototype - added tool-notes.txt, that detailes some of the
    hangups with the debugger & how to escape them.
    About to commence on total redo of ramp generation, this is a
    placeholder.
2014-10-16 WIP - phasor coming together
    Need to adapt scaling and FSM to it.
2014-10-17 More WIP.
    Basic mode is mostly complete.
2014-10-20 More WIP.
    Added one-shot FSM.
    Cleaned up gratuitous magic constants.
2014-10-23 Modality implemented.
    SJ1 selects between bistable and monostable modes.
    SJ2 selects between active lo (switch) and active high(logic) modes.
    Renamed "sw" pin to the more accurate "in."
2014-10-23 Restructuring a bit.
    Inputs are only read at end of ISR, not constantly polled.
    Trying out low power idle mode...it doesn't make much of a difference.
2014-10-24 Adding writeup to Readme, adding timing spreadsheet.
2014-10-24 Proofreading the readme.md more carefully.
2014-10-28 Adding some notes
    Notes about using a tiny programmer to reflash the device.
    Moved tool-notes.txt into the docs folder.
2014-10-28 Renaming the firmware.
    It was the default "GccApplication" name, now it's all "ServoTrigger"
2014-10-29 Tweaking docs.
    -Added some notes to programming.md
    -Improving comments in the code.
    -Added note to readme.md.
2014-12-12 Revision from collaborator and checklists
    Added mounting holes, rearranged the interface connectors.
2014-12-15 After engineering review
    PCB is ready for QC checklist.
2014-12-16 Updates based on checklist
    Undoing pour under IC.
2014-12-17 Adding test point off each trimpot
    As per discussion with Bryon we decided to add a test point off of each
    pot's ADC line in order to better automate production testing.
2014-12-19 changed micro fids to regular size
2014-12-19 created panel v10
2015-01-14 Firmware changes for CTP
    Different state machine - may or may not be the one he wants.
2015-02-18 Firmware updates, moving to production
    Adding more FSMs - toggling, astable.
    Getting some build-modularity in place for FSM selection.
2015-03-09 Adding makefile, some proofreading.
2015-03-09 Adding FSM comments to C source
2015-03-27 Updating README, fixing directory names
2015-07-07 Updating description of mode jumper.
2016-01-28 Checking in V1.1 revision
    Adding silkscreen tickboxes for standard/continuous rotation.
    Moving to "STANDARD" DRC.
2016-03-17 Adding continuous rotation build target.
    Both versions coexist in a single AtmelStudio project, just select the
    appropriate build configuration.
2016-03-18 Adjusting silk on back of board.
    Lettering was cut off by a test point.
2016-03-21 Spinning text on back of board.
    All legending reads in same direction.
2016-03-21 Updates from checklist.
2016-03-31 Updating logos from library.
    Using rounded-corner versions to save CAM time.
2016-04-01 Replacing Designer name and version number.
    They were part of the Frame, but it lost it's attributes in the library
    update.
2016-04-04 created panel v11
2020-01-16 Disable PWM after translation if LIMP is defined
    Intended for programmable servos that can be configured to go limp when
    PWM signal is lost
2020-01-16 Time multiplied with TIMEMULTIPLIER if defined
2020-01-16 Remove hardcoded Atmel Studio paths from Makefile for compatibility with GNU toolchain for avr
2020-01-16 Set FSMA and FSMB symbols in the Makefile to same value as in Atmel Studio project

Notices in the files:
parts and their libraries:
SparkFun-Aesthetics: Licensing: Creative Commons ShareAlike 4.0 International - https://creativecommons.org/licenses/by-sa/4.0
SparkFun-Aesthetics: Released under the Creative Commons Attribution Share-Alike 4.0 License
SparkFun-Aesthetics: Released under the Creative Commons
